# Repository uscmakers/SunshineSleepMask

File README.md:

## 🎞️ Project presentation

Walk through the project in the [interactive Google Slides presentation](https://docs.google.com/presentation/d/1asSZadhyUf5sEbis1G4J2R6rxChlyDanlBMHeCqUoIE/edit?usp=sharing).

## 🎞️ Presentation

## 📸 Project gallery

| | |
|:---:|:---:|
|  |  |
|  |  |

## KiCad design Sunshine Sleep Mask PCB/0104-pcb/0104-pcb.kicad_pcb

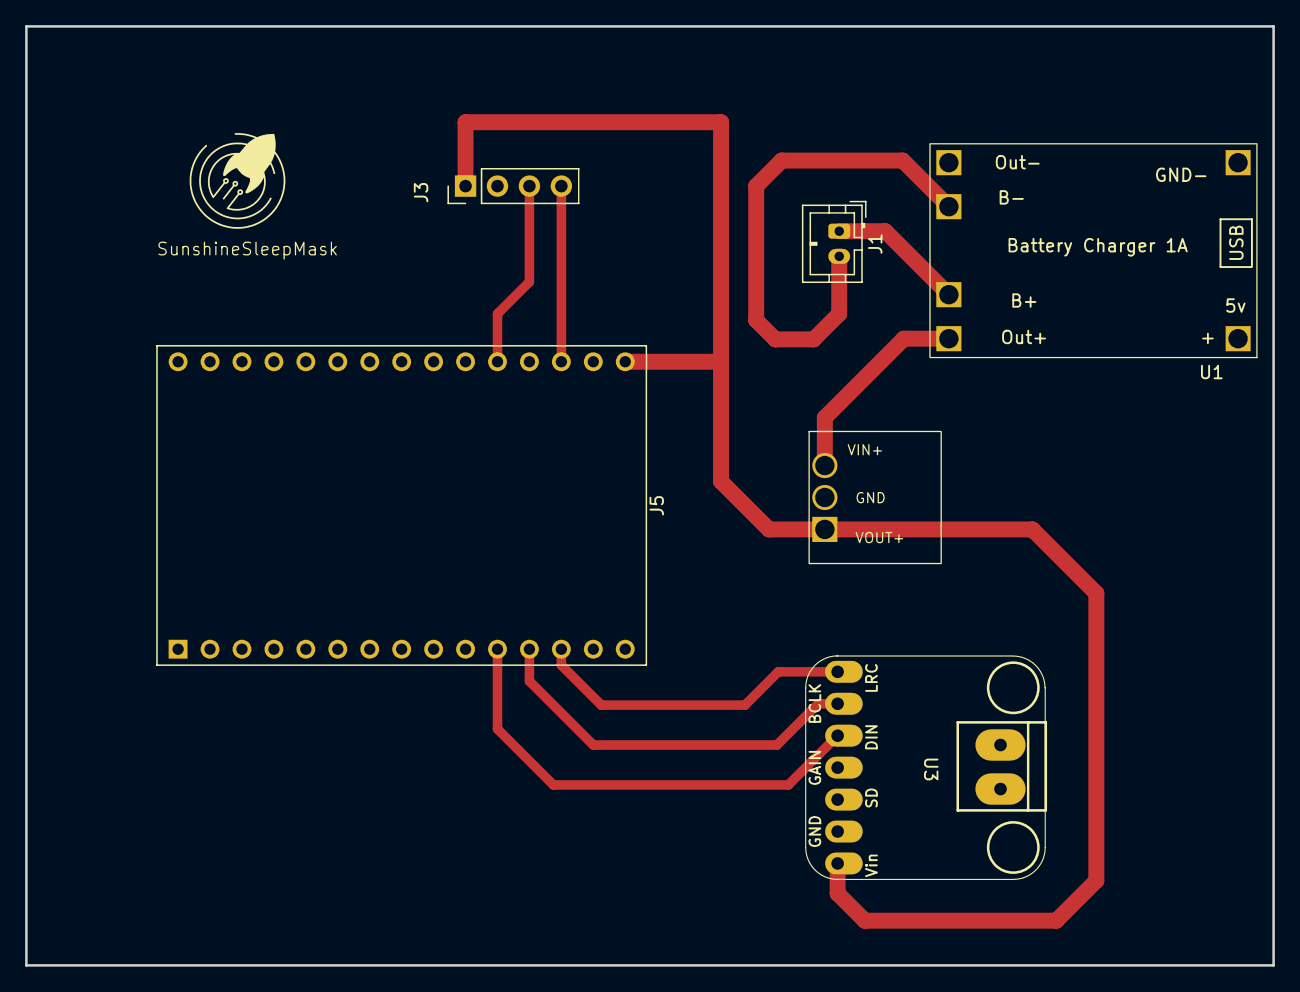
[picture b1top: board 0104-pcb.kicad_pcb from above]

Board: 2 copper layers, 99.2 x 74.7 mm, 6 parts (0 on the bottom side), 10 nets.

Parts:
J1: Conn_01x02; JST_PH_B2B-PH-K_1x02_P2.00mm_Vertical
J3: Conn_01x04; PinHeader_1x04_P2.54mm_Vertical
J5: ESP32_WROOM; ESP32_WROOM_DevKit_30Pin_Custom
U1: TP4056-18650
U2: Boost_Converter_Clay_Custom
U3: MAX98357A; adafruit-MAX98357

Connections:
+V: J1.1, U1.5 (B+)
-V: J1.2, U1.6 (B-)
GND: J3.2, J5.14 (GND), J5.29 (GND), U1.4 (OUT-), U2.2 (GND), U3.2 (GND)
unnamed: J3.1, J5.15 (VIN), U2.3 (VOUT), U3.1 (Vin)
unnamed: J3.3, J5.11 (GPIO14)
unnamed: J3.4, J5.13 (GPIO13)
unnamed: J5.27 (GPIO2), U3.6 (BCLK)
unnamed: J5.26 (GPIO4), U3.5 (DIN)
unnamed: J5.28 (GPIO15), U3.7 (LRC)
unnamed: U1.3 (OUT+), U2.1 (VIN)

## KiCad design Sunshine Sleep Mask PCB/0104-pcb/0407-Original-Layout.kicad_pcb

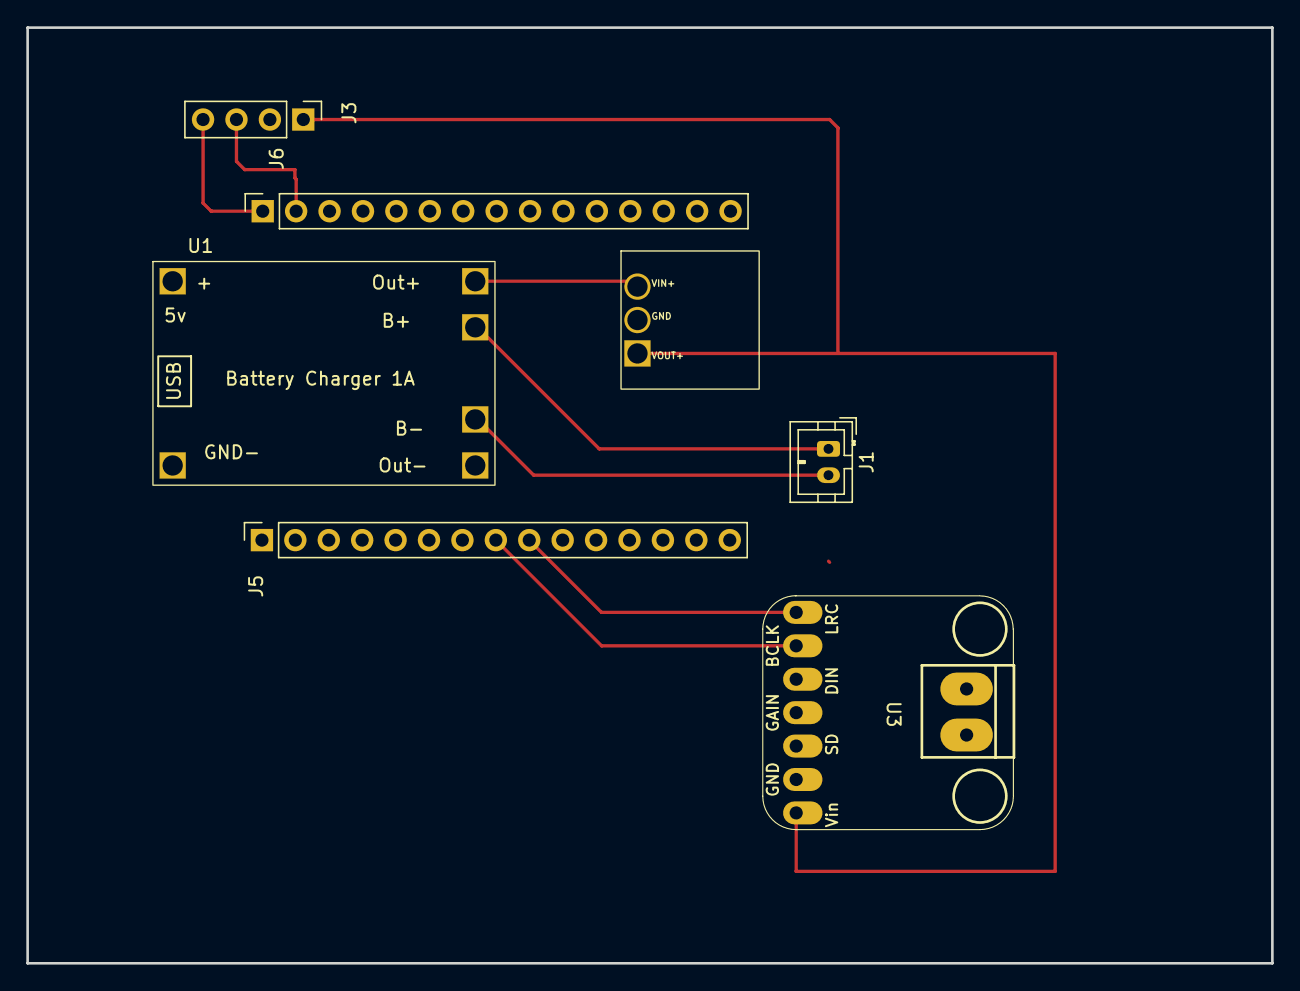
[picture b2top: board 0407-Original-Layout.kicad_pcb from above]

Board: 2 copper layers, 94.6 x 71.1 mm, 7 parts (0 on the bottom side), 11 nets.

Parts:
J1: Conn_01x02; JST_PH_B2B-PH-K_1x02_P2.00mm_Vertical
J3: Conn_01x04; PinHeader_1x04_P2.54mm_Vertical
J5, J6: Conn_01x15; PinSocket_1x15_P2.54mm_Vertical
U1: TP4056-18650
U2: Boost_Converter_Clay_Custom
U3: MAX98357A; adafruit-MAX98357

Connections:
+V: J1.1, U1.5 (B+)
-V: J1.2, U1.6 (B-)
unnamed: J3.1, U2.3 (VOUT), U3.1 (Vin)
unnamed: J3.2, J5.14, U3.2 (GND)
unnamed: J3.3, J6.2
unnamed: J3.4, J6.1
unnamed: J5.8, U3.6 (BCLK)
unnamed: J5.9, U3.7 (LRC)
unnamed: J5.10, U3.5 (DIN)
unnamed: U1.3 (OUT+), U2.1 (VIN)
unnamed: U1.4 (OUT-), U2.2 (GND)

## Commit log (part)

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2025-10-21 feat: initial color wheel
2025-11-18 updated mobile app to broadcast color hex over mqtt
2025-11-18 add microcontroller code for testing mqtt
2025-12-02 working app and esp
2025-12-03 cleaned up mobile app and debounced mqtt publishing
2026-02-19 updated flespi token
2026-02-19 Changing Fleski Token
2026-02-24 Switch LED driver from NeoPixel (WS2812) to APA102 DotStar
2026-02-24 progress on alarm page
2026-02-24 change clock_pin_1 to d4 instead of d1
2026-02-24 may edit
2026-03-03 test code for matrixLED
2026-03-24 update matrix LED code
2026-03-24 Add KiCad project files
2026-03-24 Adding Instructions
2026-03-26 alarm clock multiple alarms
2026-03-30 Edits
2026-03-31 add schematics
    rae, clay, march 30th
2026-03-31 edited
2026-03-31 We did it
2026-04-01 Clay 03/31 Edits
2026-04-01 Renamed file
2026-04-03 0104- pcb + customized footprint
    I created a new pcb editor + schematic where I copied the clay-0331. Then I made 3 customized footprints for the amplifier, charger LiPo, and for the boost converter. Similarly I was able to wire the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
2026-04-03 added the makers logo
    makers logo in 0.3x0.3in
2026-04-07 GM
    We meet with ray, we changed the wiring and we also realized we had issue with the pin connections
2026-04-08 Clay 0408 Changes
2026-04-09 7:30 04/08
2026-04-09 April 8th
2026-04-09 Newest PCB
2026-04-09 New PCB
2026-04-09 updated arduino code - LED and sound combined
2026-04-09 lil comment
2026-04-09 small update
2026-04-14 Figma UIUX
2026-04-14 UI for alarm clock working
2026-04-14 Cursor Changes
2026-04-20 Add meditation tab
2026-04-20 Cursor Changes 04/20
2026-04-21 audio file & dotenv
2026-04-21 Cursor edits 04/20
2026-04-21 Run the code april 20th
2026-04-21 repush
2026-04-21 include mp3
2026-04-21 rain sounds working
2026-04-21 updated pcb pins
2026-04-21 user add audio
2026-04-21 Fix package.json and resolve merge conflicts
2026-04-21 Modeling Figma UIUX 04/21
2026-04-22 Resolve merge and remove DS_Store
2026-04-24 Create Waterfall.mp3
    Added Subfolder for Ambient Sounds
2026-04-24 Rename Waterfall.mp3 to Waterfall.wav
2026-04-24 Cursor Changes 04-23
2026-04-24 Refactor audio handling and improve cursor functionality
2026-04-24 Update sound system, Spotify integration, and global audio behavior
2026-04-24 merged meditation.tsx into sound.tsx
2026-04-25 Create Meditation Folder
2026-04-25 Reorganize audio files into Ambient and Meditation folders
2026-04-26 Added Short Relaxation and Sunshine Simulation Code
2026-04-26 Refine alarm screen, LED settings behavior, and audio UI
2026-04-28 update app and firmware changes
2026-04-28 Spotify integration fixes, alarm scheduling, and UI improvements
2026-04-30 Expo development working app with spotify integration/controls and updated UIUX
2026-05-01 Add HealthKit setup and dev build config
2026-05-01 Added logo
2026-05-01 arudino code
2026-05-01 minor change
2026-05-01 shorter than 5 mins
2026-05-01 shorter than 5 min
